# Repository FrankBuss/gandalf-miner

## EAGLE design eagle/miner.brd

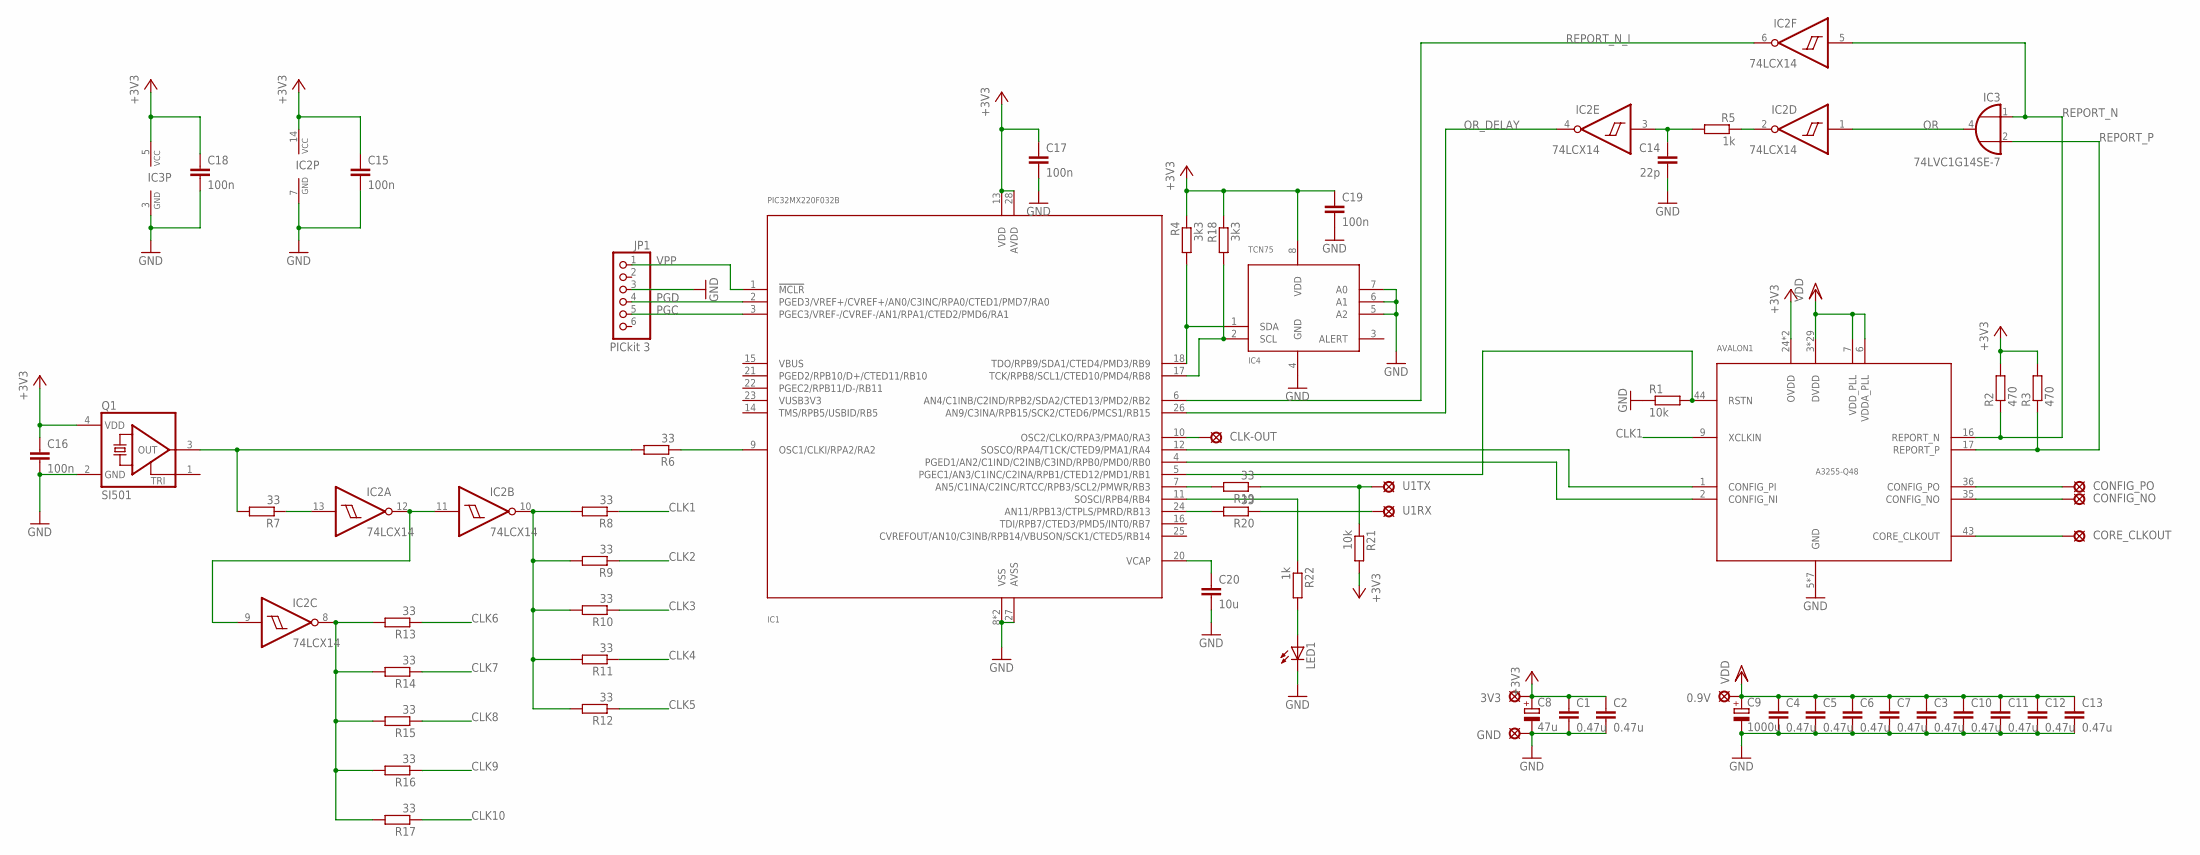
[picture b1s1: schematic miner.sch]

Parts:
0.9V, 3V3: LSP10
AVALON1: A3255-Q48; QFN48
C1, C2, C3, C4, C5, C6, C7, C10, C11, C12, C13: 0.47u; C0805
C8: 47u; 150CLZ-1010
C9: 1000u; 150CLZ-1010
C14: 22p; C0805
C15, C16, C17, C18, C19: 100n; C0805
C20: 10u; C0805
CLK-OUT: LSP10
CONFIG_NO: LSP10
CONFIG_PO: LSP10
CORE_CLKOUT: LSP10
GND: LSP10
IC1: PIC32MX220F032B; SSOP28
IC2: 74LCX14; SO14
IC3: 74LVC1G14SE-7; SC70-5
IC4: TCN75; SOIC8
JP1: PICkit 3; 1X06
LED1: LED5MM
Q1: SI501; DFN4
R1, R21: 10k; R0805
R2, R3: 470; R0805
R4, R18: 3k3; R0805
R5, R22: 1k; R0805
R6, R7, R8, R9, R10, R11, R12, R13, R14, R15, R16, R17, R19, R20: 33; R0805
U1RX, U1TX: LSP10

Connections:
+3V3: 3V3.MP, AVALON1.24 (OVDD), AVALON1.37 (OVDD), C1.1, C2.1, C8.+, C15.1, C16.1, C17.1, C18.1, C19.1, IC1.13 (VDD), IC1.28 (AVDD), IC2.14 (VCC), IC3.5 (VCC), IC4.8 (VDD), Q1.4 (VDD), R2.2, R3.2, R4.1, R18.1, R21.2
CLK1: AVALON1.9 (XCLKIN), R8.1
CLK2: R9.1
CLK3: R10.1
CLK4: R11.1
CLK5: R12.1
CLK6: R13.1
CLK7: R14.1
CLK8: R15.1
CLK9: R16.1
CLK10: R17.1
GND: AVALON1.5 (GND), AVALON1.8 (GND), AVALON1.12 (GND), AVALON1.23 (GND), AVALON1.27 (GND), AVALON1.38 (GND), AVALON1.EP-PAD (GND), C1.2, C2.2, C3.2, C4.2, C5.2, C6.2, C7.2, C8.-, C9.-, C10.2, C11.2, C12.2, C13.2, C14.2, C15.2, C16.2, C17.2, C18.2, C19.2, C20.2, GND.MP, IC1.8 (VSS), IC1.19 (VSS), IC1.27 (AVSS), IC2.7 (GND), IC3.3 (GND), IC4.4 (GND), IC4.5 (A2), IC4.6 (A1), IC4.7 (A0), JP1.3, LED1.K (C), Q1.2 (GND), R1.1
unnamed: AVALON1.44 (RSTN), IC1.5 (PGEC1/AN3/C1INC/C2INA/RPB1/CTED12/PMD1/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), R1.2
unnamed: IC1.18 (TDO/RPB9/SDA1/CTED4/PMD3/RB9), IC4.1 (SDA), R4.2
unnamed: IC1.17 (TCK/RPB8/SCL1/CTED10/PMD4/RB8), IC4.2 (SCL), R18.2
unnamed: IC1.7 (AN5/C1INA/C2INC/RTCC/RPB3/SCL2/PMWR/RB3), R19.2
unnamed: IC1.24 (AN11/RPB13/CTPLS/PMRD/RB13), R20.2
unnamed: AVALON1.1 (CONFIG_PI), IC1.12 (SOSCO/RPA4/T1CK/CTED9/PMA1/RA4)
unnamed: AVALON1.2 (CONFIG_NI), IC1.4 (PGED1/AN2/C1IND/C2INB/C3IND/RPB0/PMD0/R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)
unnamed: AVALON1.36 (CONFIG_PO), CONFIG_PO.MP
unnamed: AVALON1.35 (CONFIG_NO), CONFIG_NO.MP
unnamed: AVALON1.43 (CORE_CLKOUT), CORE_CLKOUT.MP
unnamed: Q1.3 (OUT), R6.2, R7.2
unnamed: IC2.13 (I), R7.1
unnamed: IC2.2 (O), R5.1
unnamed: C14.1, IC2.3 (I), R5.2
unnamed: IC2.9 (I), IC2.11 (I), IC2.12 (O)
unnamed: IC2.10 (O), R8.2, R9.2, R10.2, R11.2, R12.2
unnamed: IC2.8 (O), R13.2, R14.2, R15.2, R16.2, R17.2
unnamed: IC1.9 (OSC1/CLKI/RPA2/RA2), R6.1
unnamed: C20.1, IC1.20 (VCAP)
unnamed: R19.1, R21.1, U1TX.MP
unnamed: CLK-OUT.MP, IC1.10 (OSC2/CLKO/RPA3/PMA0/RA3)
unnamed: IC1.11 (SOSCI/RPB4/RB4), R22.1
unnamed: R20.1, U1RX.MP
unnamed: LED1.A, R22.2
OR: IC2.1 (I), IC3.4 (O)
OR_DELAY: IC1.26 (AN9/C3INA/RPB15/SCK2/CTED6/PMCS1/RB15), IC2.4 (O)
PGC: IC1.3 (PGEC3/VREF-/CVREF-/AN1/RPA1/CTED2/PMD6/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), JP1.5
PGD: IC1.2 (PGED3/VREF+/CVREF+/AN0/C3INC/RPA0/CTED1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), JP1.4
REPORT_N: AVALON1.16 (REPORT_N), IC2.5 (I), IC3.1 (I0), R2.1
REPORT_N_I: IC1.6 (AN4/C1INB/C2IND/RPB2/SDA2/CTED13/PMD2/R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), IC2.6 (O)
REPORT_P: AVALON1.17 (REPORT_P), IC3.2 (I1), R3.1
VDD: 0.9V.MP, AVALON1.3 (DVDD), AVALON1.4 (DVDD), AVALON1.6 (VDDA_PLL), AVALON1.7 (VDD_PLL), AVALON1.10 (DVDD), AVALON1.11 (DVDD), AVALON1.13 (DVDD), AVALON1.14 (DVDD), AVALON1.15 (DVDD), AVALON1.18 (DVDD), AVALON1.19 (DVDD), AVALON1.20 (DVDD), AVALON1.21 (DVDD), AVALON1.22 (DVDD), AVALON1.25 (DVDD), AVALON1.26 (DVDD), AVALON1.28 (DVDD), AVALON1.29 (DVDD), AVALON1.30 (DVDD), AVALON1.31 (DVDD), AVALON1.32 (DVDD), AVALON1.33 (DVDD), AVALON1.34 (DVDD), AVALON1.39 (DVDD), AVALON1.40 (DVDD), AVALON1.41 (DVDD), AVALON1.42 (DVDD), AVALON1.45 (DVDD), AVALON1.46 (DVDD), AVALON1.47 (DVDD), AVALON1.48 (DVDD), C3.1, C4.1, C5.1, C6.1, C7.1, C9.+, C10.1, C11.1, C12.1, C13.1
VPP: IC1.1 (!MCLR), JP1.1

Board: 2 copper layers, 60 parts (0 on the bottom side), 36 nets, no tracks yet.

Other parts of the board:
U$1: TCN75; SOIC8

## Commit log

2014-01-05 Avalon datasheet added
2014-01-10 first version of Avalon chip configuration
2014-01-19 added second chunk for hashing, now a valid nonce is calculated
2014-01-20 implemented a simple "getwork" miner
2014-02-09 miner with PIC
2014-03-30 FPGA implementation converted to PIC firmware
2014-03-30 PIC flash script for PICkit 2
